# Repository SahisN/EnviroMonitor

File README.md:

# DIY Indoor Environment Monitoring System

A fun and easy **DIY gadget** project to monitor your indoor environment using an **Arduino Nano**. Measure **temperature, humidity, light level, and air quality** in real-time and display it on a **2.5-inch OLED screen**. Perfect for hobbyists, makers, and anyone who wants to understand their indoor environment better.

### Link to the ardunio simulation project - https://wokwi.com/projects/448439908062672897

## Features

- Monitor **Temperature (°C/°F)**, **Humidity (%)**, **Light Level**, and **Air Quality**.  
- Real-time display on a **2.5-inch OLED screen**.  
- The device includes a multi-scene interface. A single button is used to cycle through four different viewing modes.
    ### Scene 1 — Overview
    - Displays all sensor data at once:
    - Temperature (°C)
    - Humidity (%)
    - Light level
    - Air quality level

    ### Scene 2 — Temperature & Humidity Focus
    - Enlarged temperature display
    - Enlarged humidity display
    - Ideal for quick comfort monitoring

    ### Scene 3 — Light Sensor Detailed View
    - Light level value
    - Raw LDR resistance/analog reading (for debugging)

    ### Scene 4 — Air Quality Detailed View
    - Air quality level value
    - Raw air sensor analog reading (for detailed diagnostics)

    **Scene Cycle Order:**  
    Overview → Temp/Humidity → Light → Air Quality → (loops back)

---

## Hardware Components

- **Arduino Nano** – the brain of the project.  
- **DHT22 Sensor (Adafruit)** – measures temperature and humidity.  
- **LDR Sensor** – detects ambient light levels.  
- **MQ135 Sensor** – measures air quality (CO₂ and other gases).  
- **2.5-inch OLED Display** – visualizes sensor data.  
- Breadboard and jumper wires for prototyping.

---

## Software & Libraries

- Arduino IDE  
- [Adafruit DHT library](https://github.com/adafruit/DHT-sensor-library) – for DHT22 sensor.
- [Adafruit SSD1306 library](https://github.com/adafruit/Adafruit_SSD1306) - for display  
- [Adafruit GFX library](https://github.com/adafruit/Adafruit-GFX-Library) – for display graphics.
- OLED driver library (depends on your display, e.g., `Adafruit_SSD1351` or `Adafruit_SSD1306`).  

---

## System Design

The system follows a **simple sensor → Arduino → display** flow:

    1. **Sensors**: Collect data for temperature, humidity, light, and air quality.  
    2. **Arduino Nano**: Reads the sensor values every ~2 seconds and formats them for display.  
    3. **OLED Display**: Shows live readings in an easy-to-read format (numbers, bars, or simple graphs).  

### Block Diagram

### Circuit Diagram

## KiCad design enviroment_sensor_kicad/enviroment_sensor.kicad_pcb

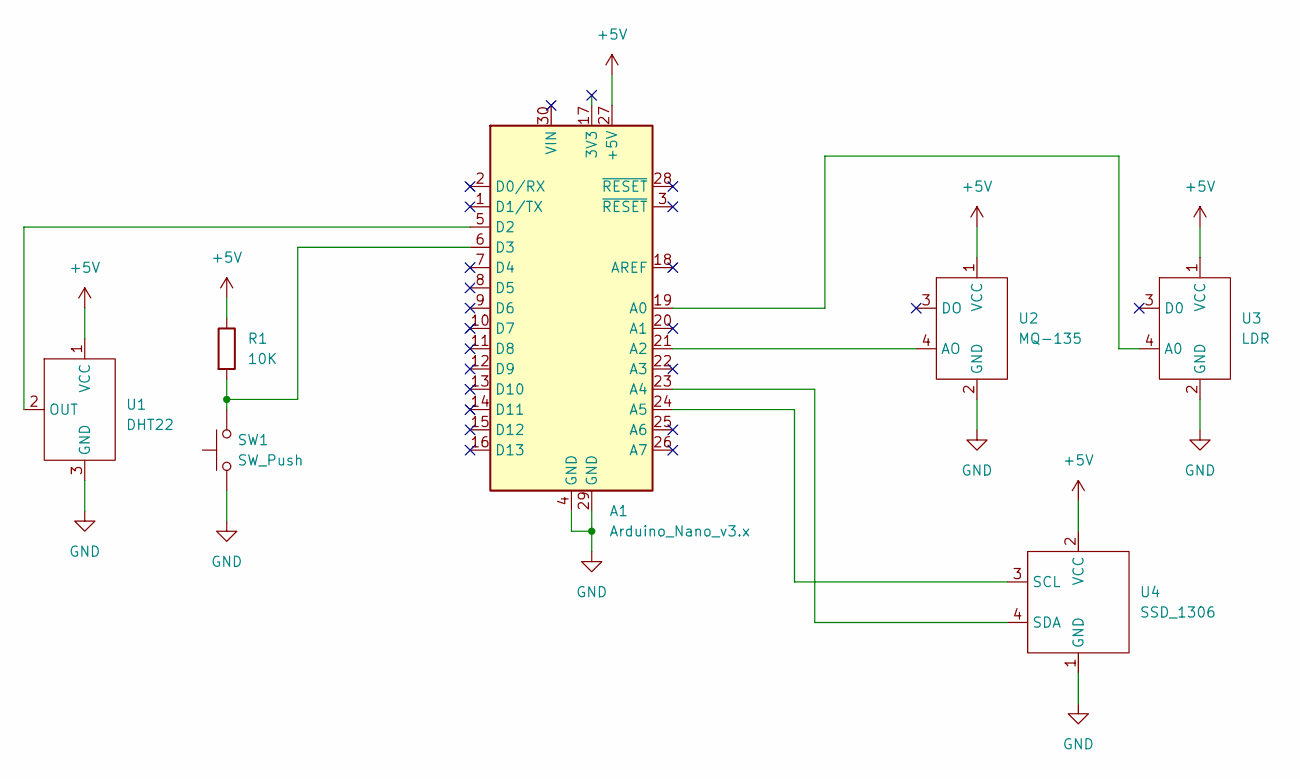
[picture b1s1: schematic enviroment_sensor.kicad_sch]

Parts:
A1: Arduino_Nano_v3.x; Arduino_Nano
R1: 10K; R_Axial_DIN0207_L6.3mm_D2.5mm_P7.62mm_Horizontal
SW1: SW_Push; SW_PUSH_6mm_H5mm
U1: DHT22; PinSocket_1x03_P2.54mm_Horizontal
U2: MQ-135; PinSocket_1x04_P2.54mm_Horizontal
U3: LDR; PinSocket_1x04_P2.54mm_Horizontal
U4: SSD_1306; SSD1306

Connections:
+5V: A1.27 (+5V), R1.1, U1.1 (VCC), U2.1 (VCC), U3.1 (VCC), U4.2 (VCC)
GND: A1.4 (GND), A1.29 (GND), SW1.1, U1.3 (GND), U2.2 (GND), U3.2 (GND), U4.1 (GND)
unnamed: A1.19 (A0), U3.4 (A0)
unnamed: A1.21 (A2), U2.4 (AO)
unnamed: A1.23 (A4), U4.4 (SDA)
unnamed: A1.24 (A5), U4.3 (SCL)
unnamed: A1.5 (D2), U1.2 (OUT)
unnamed: A1.6 (D3), R1.2, SW1.2

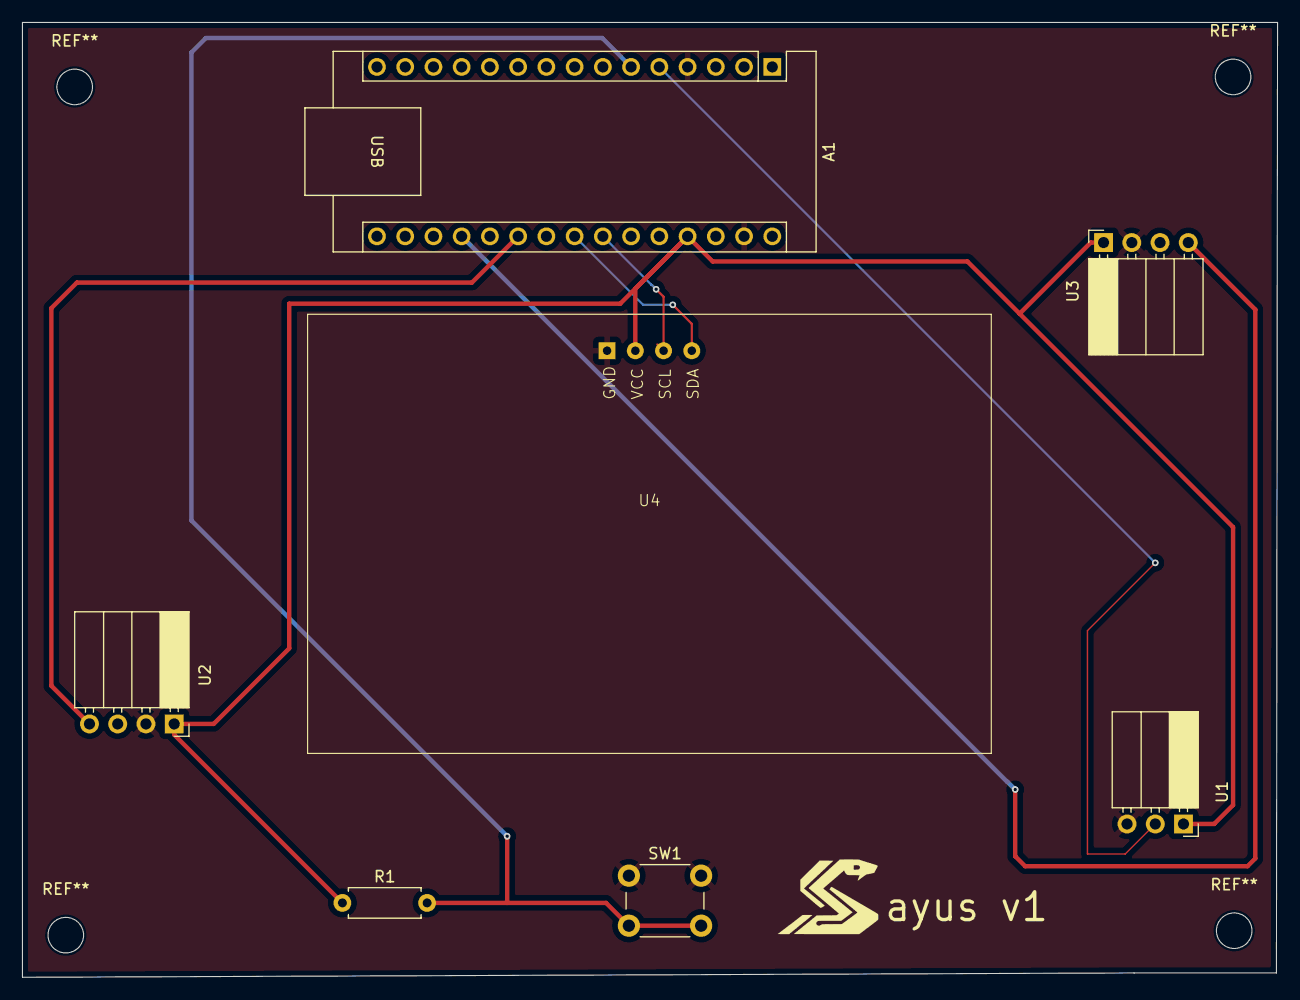
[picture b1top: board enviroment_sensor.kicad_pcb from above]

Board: 4 copper layers, 112.9 x 85.9 mm, 7 parts (0 on the bottom side), 8 nets.

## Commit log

2025-11-21 feat: added enviroment monitoring system ardunio firmware
2025-11-23 Added project documentation and fixed screen flicker
2025-11-23 fixed image path
2025-11-23 fixed image name and path
2025-11-23 Update project status in README header
2025-12-07 added dew point reading
2026-01-04 main: added screen views
2026-01-04 main: added gerber files and kicad circuit & pcb design files
2026-01-08 main: updated ui for temp & humidity, fixed screen switch bug
